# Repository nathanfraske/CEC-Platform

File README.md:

# CEC Platform

**CEC is a modular PC power-telemetry system.** Per-rail sensing modules connect
to a central Hub over a single commodity cable (RJ-45). The Hub aggregates
telemetry and forwards it to the host PC over USB. Four tiers — **Standard,
Pro, Enterprise, Mission Critical** — are built from one fundamental design with
progressively populated features.

Modules are **tier-agnostic and degrade gracefully**: any module works in any
Hub, with higher-tier features going dormant when the Hub cannot service them
and activating, without replacement, when the module is moved to a capable Hub.

This repository holds the **KiCad 10 hardware design sources** (schematics,
layouts, the shared component library), the fabrication snapshots, and the
tooling that checks them.

## PCB engineering entry points

Layout work now starts with the [frontier-directed workbench](docs/agent-directed-pcb-pipeline.md),
implemented in `src/cec_pipeline/` and exposed through one direct/MCP API.
The model authors connected placement, route and power-copper transactions;
independent native validators gate them. Legacy search engines are optional
backends, not the default decision loop.

The nine [pinned review controls](checkpoints/README.md) include portable PCB,
rule, actual footprint-library and native-report evidence. Review closure is
not manufacturing release. See the [repository module map](docs/repository-map.md)
for source, domain data, historical experiments, runtime and validation paths.

> **Ground truth.** [`CEC-Platform-Ground-Truth-Spec.md`](CEC-Platform-Ground-Truth-Spec.md)
> is the canonical specification and holds precedence over everything else,
> including [`CLAUDE.md`](CLAUDE.md). Read the spec before making any design
> decision. Spec revision: **v1.1.0 (2026-06-09), controlled baseline** (semantic
> versioning; the pre-release v1.0–v3.11 working log is retained in spec §11.1).
> Working-summary revision: **2026-06-09**.

---

## Boards

| Board | Directory | Tier | MCU | Ports | Host link | BOM target (100q) |
|---|---|---|---|---|---|---|
| Hub Standard | [`beta/hub-standard-rev2`](beta/hub-standard-rev2) | 1 | ESP32-S3-WROOM-1-N16R8 | 4 | USB Full Speed | ~$36 |
| Hub Pro | [`hubs/hub-pro`](hubs/hub-pro) | 2 | ESP32-P4 | 8 | USB High Speed | ~$45 |
| Hub Enterprise | [`hubs/hub-enterprise`](hubs/hub-enterprise) | 3 | ESP32-P4 + secure element | n/a | USB HS (+ optional 1000BASE-T1) | ~$50 |
| Hub Mission Critical | [`hubs/hub-mission-critical`](hubs/hub-mission-critical) | 4 | ESP32-P4 + crypto | n/a | redundant uplinks | ~$80 |
| 24-pin ATX module | [`beta/atx-24pin-rev3`](beta/atx-24pin-rev3) | Standard | per module spec | – | – | $35 |
| EPS 8-pin module | [`beta/eps-8pin-rev3`](beta/eps-8pin-rev3) | Standard | per module spec | – | – | $32 |
| PCIe 8-pin 2-port | [`beta/pcie-8pin-2port`](beta/pcie-8pin-2port) | Standard | per module spec | – | – | $38 |
| PCIe 8-pin 3-port | [`beta/pcie-8pin-3port`](beta/pcie-8pin-3port) | Standard | per module spec | – | – | ~$42 |
| 12VHPWR Standard module | [`beta/12vhpwr-standard`](beta/12vhpwr-standard) | Standard | per module spec | – | – | $49 |
| 12VHPWR Pro module (lead) | [`modules/12vhpwr-pro`](modules/12vhpwr-pro) | Pro | ESP32-P4 | – | – | $98–$99 |

Enterprise and Mission Critical are specified at platform-summary level only
until first customer requirements land (see **OQ-7**).

---

## The universal interface (LOCKED)

Every board — every Hub, every module, every tier — uses the same **shielded
RJ-45 (8P8C)** connector with a **locking boot** as the default shipped variant.
Mini-Fit Jr is retired platform-wide. The shared parts that implement this
interface (RJ-45 FTP jack, SK6812 LED chain, ESP32 module, power input — plus
the optional Enterprise/MC over-voltage protection network, OQ-8) live in [`lib/`](lib) so one change propagates
to every board.

### Pin allocation

| Pin | Cat5e pair | T568B color | CEC function | Tiers |
|---|---|---|---|---|
| 1 | Pair 1 | White-orange | VCC (+5VSB power) | All |
| 2 | Pair 1 | Orange | GND (power return) | All |
| 3 | Pair 3 | White-green | CAN1_H (control + low-rate telemetry) | All |
| 4 | Pair 2 | Blue | STREAM_P (RS-485 data, module → Hub) | Pro+ |
| 5 | Pair 2 | White-blue | STREAM_N (RS-485 data, module → Hub) | Pro+ |
| 6 | Pair 3 | Green | CAN1_L | All |
| 7 | Pair 4 | White-brown | AUX_REF (precision reference) | Pro+, pending OQ-3 |
| 8 | Pair 4 | Brown | DETECT / module-ID (analog single-wire sense) | All |

- **Power.** VCC is +5VSB on a single pin; GND returns on a single pin (no
  paralleling). Hubs take **bulk 5VSB on a dedicated 2-pin power-in connector**
  from the 24-pin module (spec §2.7) and distribute it to ports over RJ-45 VCC, so
  no single jack carries the trunk and per-port VCC stays comfortable. The RJ-45
  connector is still rated **≥ 1.5A**, and firmware **caps aggregate SK6812 LED
  current** (OQ-2). The VCC series protection resistor is sized together with the
  power budget, not independently.
- **Control — CAN.** All control and command traffic lives entirely on CAN, on
  pair 3, for every tier. Classical CAN at 500 kbps on Standard; CAN-FD on Pro
  and above. Transceiver TJA1051T/3; fixed **120 Ω split termination at the Hub**.
- **Streaming — RS-485.** High-bandwidth telemetry only, one direction
  (module → Hub), on pair 2. Present on **Pro modules and Pro+ Hubs only**;
  Standard leaves pair 2 unused and terminated at the module side.
- **DETECT.** Analog single-wire identity and presence sense: a precision
  resistor from pin 8 to GND on each module, read by the Hub through a fixed
  pull-up to VCC as an ADC divider. Open line ≈ VCC = no module. Resistor code
  table pending (OQ-6).
- **Protection.** Standard and Pro do **not** populate per-pin PoE/over-voltage
  protection — accidental PoE injection isn't a design target there. A per-pin
  TVS array plus series limiting resistors (PoE-survivable to ~57V) is an open
  question for Enterprise/Mission Critical (OQ-8).

See spec [§2](CEC-Platform-Ground-Truth-Spec.md) for the full interface detail.

---

## Repository layout

```
cec-platform/
  lib/                       # shared library: the locked universal interface
    cec.kicad_sym            #   symbols (authored in the KiCad Symbol Editor)
    cec.pretty/              #   footprints (RJ-45 FTP jack, SK6812, ESP32, power input; protection net is Enterprise/MC, OQ-8)
    3dmodels/                #   3D models referenced by footprints
  hubs/
    hub-standard/            # Tier 1 — ESP32-S3, 4 ports, classical CAN, USB FS
    hub-pro/                 # Tier 2 — ESP32-P4, 8 ports, classical CAN + RS-485, USB HS
    hub-enterprise/          # Tier 3 — platform-summary only for now (OQ-7)
    hub-mission-critical/    # Tier 4 — platform-summary only for now (OQ-7)
  modules/
    atx-24pin/               # Standard (superseded line)
    atx-24pin-rev2/          # Standard (current 24-pin line)
    eps-8pin/                # Standard
    pcie-8pin-2port/         # Standard (2 ports / 4 connectors)
    pcie-8pin-3port/         # Standard (3 ports / 6 connectors)
    12vhpwr-standard/        # Standard
    12vhpwr-pro/             # Pro (lead Pro module)
  fab/                       # tagged release snapshots of exactly what was sent to the board house
  firmware/                  # module firmware: shared ESP-IDF components, per-app trees, RTL
  corpus/general/            # cross-project rules corpus (SB-13; linted for provenance)
  tests/                     # pipeline unit tests + the golden-board regression (SB-08)
  docker/                    # the routing-container compute plane (kicad-cli/pcbnew 10 + JRE)
  scripts/                   # kicad-cli wrappers, CI helpers, and the agentic routing/synthesis plane
  CEC-Platform-Ground-Truth-Spec.md   # canonical spec (precedence over all)
  CLAUDE.md                  # operating guidance / working summary of the spec
  README.md
  LICENSE  NOTICE            # Apache-2.0
```

Each board is its own KiCad project. The universal-interface parts are sourced
from `lib/` rather than duplicated per board, and library tables use
project-relative paths (`${KIPRJMOD}`) — **never** absolute paths.

**Firmware lives in [`firmware/`](firmware/)** — consolidated from the
former `cec-24pin-idf` and `cec-eps-idf` repos (subtree-imported with
history) plus the 12VHPWR prototype's RTL + ESP32-P4 app: shared
ESP-IDF components under `firmware/esp/components/`, the prototype
(dev-board/perfboard) apps under `firmware/esp/proto/` — the flat
`firmware/esp/<name>` level is reserved for production apps matching
`modules/<name>` — and the GW5A acquisition RTL under `firmware/rtl/` with its
simulation gate. Pin maps live next to the KiCad projects that define
them; `firmware/FOLLOWUPS.md` tracks deferred work, and
`.github/workflows/firmware-ci.yml` builds all three apps + runs the
RTL sim on every firmware push (toolchain pins in `versions.env`).

---

## Toolchain

- **KiCad 10** (current stable, 10.0.x series). The `.kicad_*` file format is
  forward-only: a board saved in 10 will not open in 9. Keep every local install
  and any CI/container on the same major version.
- **`kicad-cli`** ships with KiCad and runs headless; it must be on `PATH`. For
  CI or a container, use the official KiCad Docker image rather than a full GUI
  install.

### Checks and outputs

Wrapper scripts in [`scripts/`](scripts) drive `kicad-cli`. Each prefers a local
`kicad-cli` and otherwise falls back to the official KiCad Docker image
(override the tag with `KICAD_IMAGE`, default `kicad/kicad:10.0`).

```bash
# Electrical rule check (schematic). Exit 0 = clean, 5 = violations.
scripts/erc.sh beta/hub-standard-rev2/hub-standard-rev2.kicad_sch

# Design rule check (layout). Exit 0 = clean, 5 = violations.
scripts/drc.sh beta/hub-standard-rev2/candidate/hub-standard-rev2-candidate.kicad_pcb

# Connectivity netlist and BOM, for checking against the spec.
scripts/netlist.sh beta/hub-standard-rev2/hub-standard-rev2.kicad_sch
scripts/bom.sh     beta/hub-standard-rev2/hub-standard-rev2.kicad_sch

# Top-side render for a quick silk/placement look.
scripts/render.sh  beta/hub-standard-rev2/candidate/hub-standard-rev2-candidate.kicad_pcb

# Fab package (gerbers + drill + pick-and-place) into the gitignored build/ dir.
scripts/fab.sh     beta/hub-standard-rev2/candidate/hub-standard-rev2-candidate.kicad_pcb

# CI sweep: ERC over every schematic, DRC over every layout. A board with a
# fab/<board>-* snapshot is ALWAYS checked, DRAFT marker or not; the gate fails
# on ERROR-level violations (warnings stay visible in the build/ reports).
scripts/check-all.sh

# Repo hygiene: no Mini-Fit Jr footprints, no absolute library paths, and the
# corpus provenance lint (corpus/general/ + scripts/constraints/).
scripts/checklist.sh
```

Reports and fab outputs are written under `build/` (gitignored). Fab packages
are committed only as tagged release snapshots under `fab/<rev>/`.

### Model-directed PCB work (Python / MCP)

Use [`src/cec_pipeline`](src/cec_pipeline) through
`python3 scripts/cec_agentic_workbench.py --workspace .cec/campaign`.
The frontier model chooses explicit geometry; independent native/current/
Kelvin/assembly receivers gate each private candidate. See the
[workflow guide](docs/agent-directed-pcb-pipeline.md) and
[repository map](docs/repository-map.md).

The old self-hosted Route/Synthesize workflows, overnight launchers, local
wave manager, legacy compute MCP registration and wave wakeup bridge are
retired. Shared CAD/physical libraries remain importable for receiving and
regression coverage, but their old autonomous CLI entry points fail closed.
Board-local `pipeline-policy.json` files own the approved requirements;
loading one no longer imports the old wave runner. Retirement inventory and
recovery instructions are in `docs/legacy-job-retirement-2026-11-05.json`.

### Self-contained & reproducible (clone parity)

A plain `git clone` is a full-parity project — no dependency on a machine's
global KiCad libraries:

- **Pinned toolchain.** The KiCad version is pinned in
  [`versions.env`](versions.env) (major 10, the 10.0.x series); the scripts and
  CI read it. The `.kicad_*` format is forward-only.
- **Vendored parts.** Official and third-party symbols/footprints are copied into
  [`lib/vendor/`](lib/vendor) and their 3D models into
  [`lib/3dmodels/`](lib/3dmodels), all referenced by `${KIPRJMOD}`-relative
  paths. `scripts/vendor-libs.sh` brings them in at the pinned library tag.
- **Enforced.** `scripts/checklist.sh` (run in CI) fails if any design file uses
  a machine-global `${KICAD*_DIR}` or an absolute path — the signal that a part
  still needs vendoring.

---

## Design-review checklist

A recurring pass, enforced in part by `scripts/checklist.sh`:

- No Mini-Fit Jr footprints remain anywhere; all module-to-Hub connectors are
  RJ-45 8P8C.
- Pinout on every board matches the locked pin allocation table above.
- PoE/over-voltage protection is not populated on Standard/Pro; on Enterprise/MC
  it follows OQ-8.
- The RS-485 pair (pins 4 and 5) and its receivers exist only on Pro and above;
  Standard leaves pair 2 unused and terminated at the module side.
- CAN termination is a fixed 120 Ω split at the Hub.
- Power-netclass trace width covers the trunk worst case; the firmware LED
  current cap is reflected in the design intent.
- Libraries and 3D models are vendored in-repo and referenced by
  `${KIPRJMOD}`-relative paths only (no machine-global or absolute paths).
- BOM totals are in line with the spec targets.

---

## Open questions

Design decisions that are **not** settled in the spec. Do not assume an answer;
surface it. Summarized here, full text in spec [§9](CEC-Platform-Ground-Truth-Spec.md).

| ID | Topic | Spec recommendation |
|---|---|---|
| OQ-1 ✓ locked | Hub bulk power → dedicated 2-pin +5VSB power-in from the 24-pin module; RJ-45 VCC distributes per-port (spec §2.7) | Resolved 2026-05-30 |
| OQ-2 | LED current cap value and max LED state to budget | Confirm a firmware cap |
| OQ-3 | Precision reference: distributed AUX_REF (pin 7) vs. local REF3033 | Path B (local REF3033) |
| OQ-4 | Cable-length SKUs and any-length policy | Pending; interacts with OQ-3 |
| OQ-5 | RS-485 topology: per-port point-to-point vs. shared multidrop | Per-port (working basis) |
| OQ-6 | Module-ID resistor encoding table | Pending module/tier list |
| OQ-7 | Fully specify Enterprise/Mission Critical now, or summary-level | Summary-level for now |
| OQ-8 | Per-pin PoE/over-voltage protection on Enterprise/MC (TVS + series-R, ~57V); Standard/Pro don't populate it | Pending Ent/MC requirements |

Two consequences worth calling out for layout work:

- With **OQ-1 locked** (dedicated 2-pin power-in), the full 5VSB trunk runs on the
  dedicated power-in and the Hub's internal distribution, while each RJ-45 VCC pin
  carries only one module. The **power-netclass minimum trace width** and the
  board `.kicad_dru` still wait on **OQ-2** (the LED cap) to fix the worst-case
  current.
- **AUX_REF on pin 7** is provisional pending **OQ-3**; treat it as such.

---

## Status

This is an early-stage hardware repository. The directory structure, shared-
library home, tooling, CI, and documentation are in place. The KiCad design
artifacts land per board over time: symbols, library-driven schematics, and
library tables can be drafted in-repo (then verified with ERC and the exported
netlist), while **PCB routing geometry** is done interactively in the KiCad 10
GUI.

**Carried action item:** the Hub Standard and 12VHPWR schematics still show
Mini-Fit Jr footprints and must be re-cut to RJ-45 before any board order. They
are the stale artifacts; the spec is current.

---

## Contributing

- The spec wins. If a change to a locked decision seems warranted, propose a
  spec revision first rather than diverging in a board.
- Do not resolve an open question (OQ-1…OQ-7) by assumption — surface it.
- Keep library paths project-relative (`${KIPRJMOD}`); never commit absolute
  paths. Vendor any official/third-party part you use
  (`scripts/vendor-libs.sh`) so a clone stays self-contained, and keep the
  toolchain on the pinned KiCad 10 (`versions.env`).
- Run `scripts/check-all.sh` and `scripts/checklist.sh` before pushing layout or
  schematic changes.
- Commit fab outputs only as tagged release snapshots under `fab/<rev>/`, not as
  routine churn.

---

## License

Copyright 2026 Nathan M. Fraske.

Licensed under the **Apache License, Version 2.0**. You may not use the files in
this repository except in compliance with the License. See [`LICENSE`](LICENSE)
for the full text and [`NOTICE`](NOTICE) for attribution; a copy of the License
is also available at <http://www.apache.org/licenses/LICENSE-2.0>.

Unless required by applicable law or agreed to in writing, work distributed
under the License is distributed on an "AS IS" BASIS, WITHOUT WARRANTIES OR
CONDITIONS OF ANY KIND, either express or implied.

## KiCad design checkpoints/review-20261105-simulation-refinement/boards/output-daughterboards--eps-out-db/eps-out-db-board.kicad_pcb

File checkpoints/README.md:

# Native review controls

`current.json` pins one receipt by its exact SHA-256, never by file age. The
November 4 snapshot contains nine saved PCB families, their actual footprint
libraries, fresh native DRC reports, original reports and source provenance.
It is a portable review checkpoint, **not a fabrication release**. Its native
totals are zero opens, zero errors, zero exclusions and 283 warnings. Retained
EPS field-policy findings are separate from native DRC.

`review-20261104-final` preserves the pre-overhaul layout controls.
`review-20261104-overhaul` adds the independently received, visually reviewed
Hub route-shortening pilot; all other board geometry is identical. Its origin
receipt retains the explicit work order, parent/child identities and plot
identities. `current.json` selects this newer review checkpoint explicitly.

The frontier-directed workbench copies these controls into private jobs. It
cannot overwrite them or silently select a different schematic/PCB revision.
`fork` changes only the campaign's selected working parent after receiving
and visual review. Runtime jobs and plots belong outside this directory.

Footprint-library URIs are relocated; actual footprint file bytes, library
names and enable flags are retained. No library is synthesized from the
embedded board pads. A fresh checkout requires KiCad 10.x and the documented
native reporting build to repeat measurements, but not the original author's
Windows review directory to inspect the saved evidence.

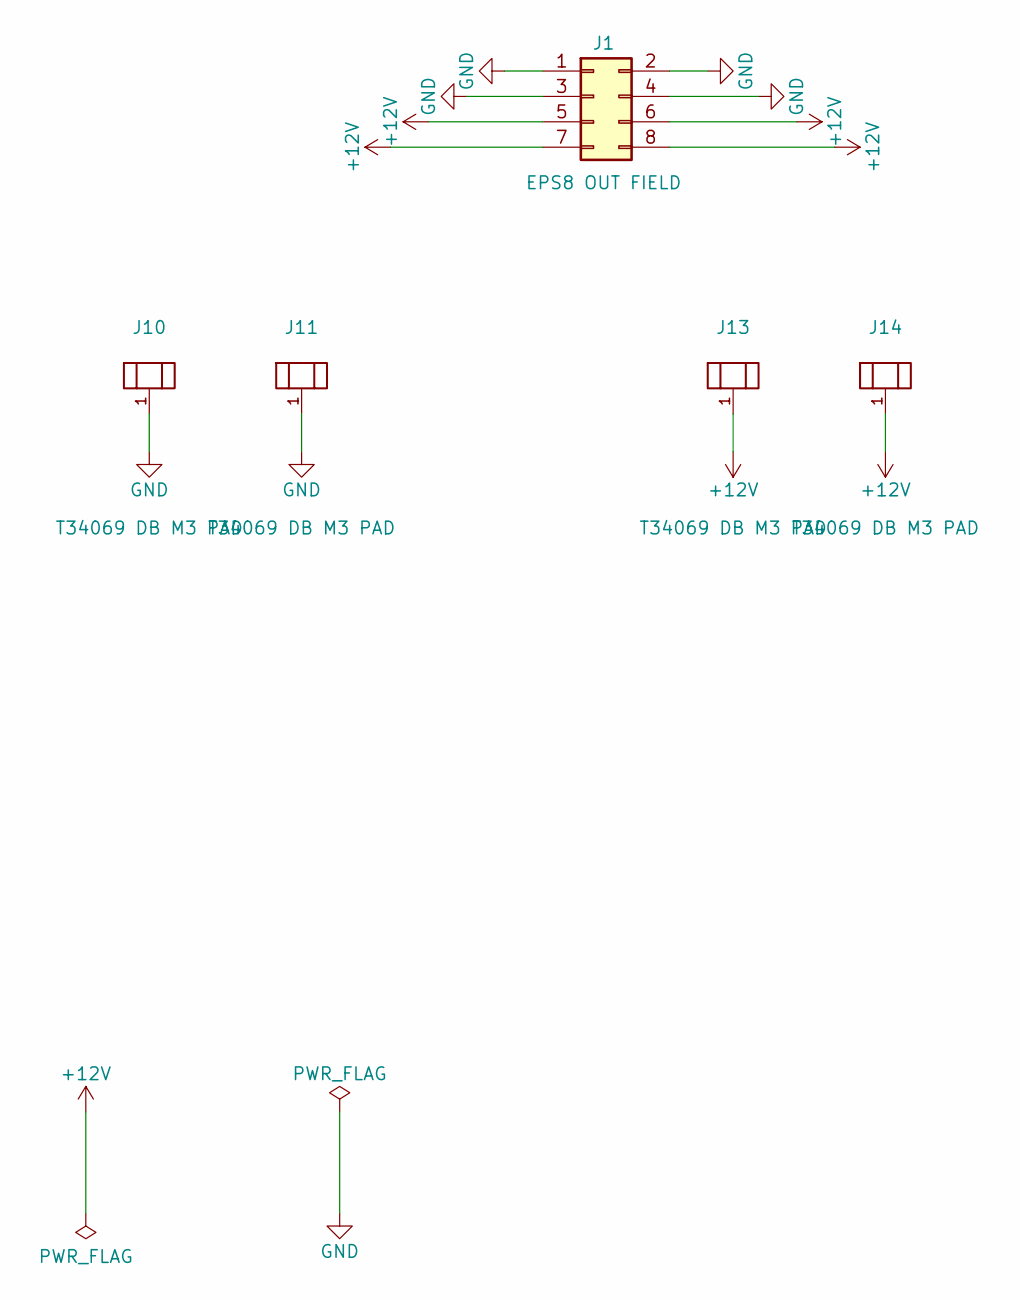
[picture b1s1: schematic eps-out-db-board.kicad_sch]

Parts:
J1: EPS8 OUT FIELD; EPS8_Daughterboard_Field_P4.20mm
J10, J11, J13, J14: T34069 DB M3 PAD; XFCN_T34069_Daughterboard_BoltPad_M3_PROVISIONAL

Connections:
+12V: J1.5, J1.6, J1.7, J1.8, J13.1, J14.1
GND: J1.1, J1.2, J1.3, J1.4, J10.1, J11.1

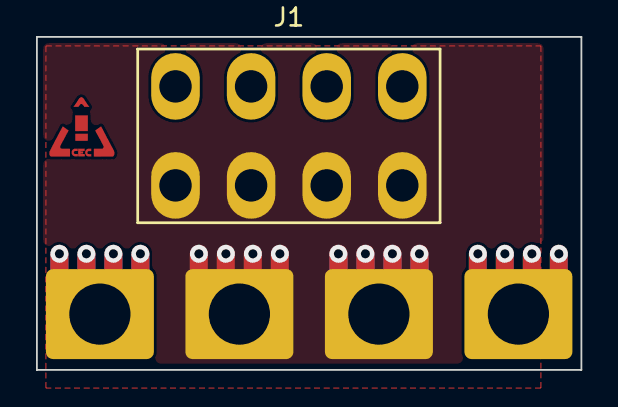
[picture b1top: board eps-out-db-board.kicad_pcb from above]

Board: 4 copper layers, 30.2 x 18.5 mm, 6 parts (0 on the bottom side), 2 nets.

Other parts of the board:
LOGO1: CEC_Logo_Copper_Small

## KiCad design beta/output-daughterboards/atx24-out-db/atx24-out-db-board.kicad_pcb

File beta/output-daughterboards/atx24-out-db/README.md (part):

# 24-pin ATX output daughterboard — BETA-1

> **XFCN PROTOTYPE SUPERSESSION (2026-08-12):** the live schematic and PCB now
> use four XFCN T34069 M3 bolt pads for `+12V`, `+5V`, `+3V3`, and `+5VSB`,
> plus two XFCN TTR32100127-0600 M3 bolt pads for `GND`. The TE blade history
> below remains as design provenance, not current implementation authority.
> The former PCB-only `SR1`–`SR6` pads were no-net placeholders, did not form a
> measurement circuit, and are retired. A future connector-health/remote-sense
> feature must be introduced as a complete schematic, mating, ADC-protection,
> and firmware contract rather than as anonymous copper provisions. See
> `docs/standard-xfcn-terminal-integration-handoff-2026-08-12.md`.
> The live compact outline is **54.0 × 21.3 mm** (11.8% less area than the
> 61.0 × 21.38 mm predecessor). The four control circuits now use a compact
> **Samtec TSW-102-16-G-D-RA 2×2 right-angle male**, mating the main board's
> **SSQ-102-03-G-D 2×2 vertical socket**. Pin order is Samtec odd/even by
> column: 1=`-12V`, 2=`PS_ON#`, 3=`PWR_OK`, 4=`GND`. The `-16` style's
> 8.13 mm mating length satisfies the calculated ≥6.4 mm engagement floor;
> first-article alignment and engagement remain required.

Passive connector-daughterboard for the 24-pin ATX module's OUTPUT side, per
spec **§2.8 v1.4.0** (`CEC-Platform-Ground-Truth-Spec.md`) and the owner
ruling `docs/standard-tier-review/SYNTHESIS-beta-plan.md` §D-5a. Mates with
the main board's `TB1`–`TB9` Keystone 3586 universal blade clips (TB symbols
exist in `modules/atx-24pin-rev3`'s **schematic**, commit `b76a62a`; **no
clip placement exists on any main-board PCB yet** — this board's tab grid is
the authoritative mating drawing, see "Keying") and reproduces the full
24-circuit ATX output pin map for a bare pigtail or a future MODDIY-class
vertical header. **No active or passive components** — connector bodies and
fan-out copper only, per the ratified "no components beyond the connector
body and its fan-out copper" text.

> **ITERATION 7 (2026-07-06, owner-ratified) — READ FIRST, supersedes the
> iteration-5 numbers below where they differ.** Main-board mate changed:
> Keystone **3557 clip → TE 63969-1 FASTON .250 PCB RECEPTACLE** (vertical/
> top entry; the DESIGNED mate for the 63951-1 blade — rev-E dwg note 3
> puts our 0.81 mm thickness at its design centre, retiring the
> 27%-over-centre fit item; 22.9 A @ 30 °C rise per TE 108-1706; 63968-1 =
> same-land low-insertion-force fallback; LCSC C2961150, stock ~5 =
> restock watch, DigiKey depth). **ORIENTATION (owner requirement, proven
> from `lib/datasheets/TE_63969_customer_drawing_revE.pdf` and
> checker-asserted):** the receptacle's two Ø1.40 holes at 5.08 mm pitch
> run **perpendicular to the row**, along the descending blade's plane —
> plan-congruent with the blade's own leg holes; the blade's bottom edge
> enters the slot edge-wise. Along-row footprint is therefore only the
> receptacle's ~3.7 mm across-thickness depth (UN-DIMENSIONED on rev E —
> **depth ≤ 4.0 mm is the #1 sample-gate item; above it, atx24 falls back
> to a 6.3 pitch**): pitch floor 3.7 + 0.5 = **4.2 mm**; pitches now
> **atx24 4.2 / eps 4.7 / pcie 5.2**. Joint counts re-ratified at
> 22.9 A/125% (18.32 A allowable per joint): **atx24 10 tabs** (3V3 gains a
> second joint at 24.0 A basis; GND ×4 = 18.0 A/joint = 127% hairline,
> surfaced), **eps holds 6/cable** (17.33 A = 132%), **pcie 6/cable**
> (3/polarity; 2/polarity was 19.5 A = 117% FAIL). Boards: **atx24 61.0 ×
> 21.4, eps 28.5 × 20.0, pcie 31.0 × 20.0 mm** (pcie GROWS — the +2
> ratified joints outweigh its pitch win; honest number). Seating: float
> 12.41 mm unchanged; the 8.38 mm receptacle top is cleared by **4.03 mm**;
> detent-hole engagement at nominal float is NOT established (retention may
> be spring-friction only — sample item, with gang insertion force). Full
> record: `docs/standard-tier-review/blade-fit-check-2026-07-04.md`
> **addenda 6–7**.

> **ITERATION 5 (2026-07-05, owner) — READ FIRST, supersedes the iteration-4
> numbers below where they differ.** Main-board clip part changed: Keystone
> **3586 (SMD) → 3557 bare top-entry clip** (THT, UL 30 A @ 500 V AC; the
> "3557-2" this repo vendored earlier is the 2-in-1 HOUSED holder, a
> different product — naming corrected; 3586 stays vendored as the SMD
> fallback). Clip rotated slot-perpendicular-to-wall; its **leg pair runs
> ALONG the row** (verified from the catalog mounting details — this
> contradicts the leg-parallel-to-jaw assumption and caps the win): pitch
> floor = 3.4 leg pitch + 2.4 pad + 0.5 solder web = **6.3 mm**, pitches now
> **atx24 6.3 / eps 6.7 / pcie 7.2** (keying margins 1.00/0.75/1.35, teeth
> re-verified). Boards: **atx24 69.5 × 21.4, eps 38.5 × 20.0, pcie 26.6 ×
> 20.0 mm**. Seating: uniform 4.34 mm leg row, float 12.41 mm at 1.0 mm tip
> clearance; the taller 10.2 mm clip's top is cleared by 2.21 mm; engagement
> now spans the clip's full interior. atx24 also swaps its signal stub: the
> 2×5 header is RETIRED for a **1×4 right-angle blind-mate pin header**
> (long-tail Dupont class, pins down past the edge parallel to the blades,
> single-motion drop-in; NEW pin map 1=−12V, 2=PS_ON#, 3=PWR_OK, 4=GND) plus
> **six DNP sense-return pads SR1–SR6** (OQ-88 provision form only). #1
> fit-check item: the 0.81 mm FASTON tab is ~27% over the clip's 0.64 mm
> fuse-blade design centre (inside the published .020–.032 acceptance, at
> its ceiling — stiffer grip expected, sample-gated). Full record:
> `docs/standard-tier-review/blade-fit-check-2026-07-04.md` **addendum 5**.

DRAFT (no fab yet — the OQ-86 physical fit-check sample gate is still open).

## Posture — vertical card, tabs blade-DOWN (owner sketch, 2026-07-05)

This board is a small vertical card standing perpendicular to the main board
(owner ruling 2026-07-04/05, unchanged). The connector form went through
three same-day iterations on 2026-07-05 and is settled by the **owner's
sketch** (the final ruling; the two earlier forms — TE 63849-1
straight-tab/side-entry, then a mis-modeled "blade hangs past the edge
in-plane" reading of the 63951-1 — are retired, record in
`docs/standard-tier-review/blade-fit-check-2026-07-04.md` addendum 3):

The tabs are **TE 63951-1** (RIGHT-ANGLE FASTON .250 — "the blade that has
the 90 degree rotation in it," owner). The part is a flat in-plane **L
stamping**: the blade runs along the leg-pitch axis past the blade-side leg,
standing **2.54–8.89 mm off its seating face** (TE dwg C=63951 rev L2,
`lib/datasheets/TE_63951-1.pdf`). Mounted per the sketch: the two legs go
**horizontally** through this board's face, the 5.08 mm leg pitch runs
**vertically** (legs stacked one above the other), and the blade therefore
points **straight down**, descending past this board's bottom edge at the
2.54–8.89 mm Z-standoff — *"It needs to align vertically so it can actually
point down and slot into the clip."* The whole assembly drops vertically;
each blade enters its main-board Keystone 3586 clip's **top-entry** jaws
broadside (the clip's native auto-blade-fuse mode, Keystone dwg 3586). The
board's own bottom edge **floats clear of the main board** — *"the TAB does
the reaching down, not the board"* — no board material or copper crosses
Edge.Cuts; only the tab's off-board descender passes below the edge level,
offset from the board plane with no conflict.

**Board axes**: X = length (FREE dimension, minimized opportunistically);
Y = height. **The ≤15 mm height cap is EXPLICITLY RELAXED by the owner for
the iteration-4 compact form** (owner follow-up on the 145 mm iteration-3
board: *"Good lord those are long, can the agent stack the blades right
next to each other and put them below the pinout? That should tell us how
tall these are really going to be"*) — the deliverable is the honest
minimum height of the two-band stack.

**Measured final size**: **69.5 × 21.4 mm** (length × height). The tab row
returned BELOW the field (two-band stack: field + corridor on top, packed
tab row underneath), halving the length (145.1 → 72.8 mm) at a true height
cost of 13.6 → 21.4 mm. Height decomposition (all measured constants):
0.4 top margin + 10.2 field + 0.1 gap + 2.25 corridor (4 In2 lanes) +
0.3 lane-to-pad clearance + 7.58 tab pad band (2 × 3.79) + 0.55 edge
margin. Length is now tab-row-driven (9 × 8.4 mm + margins ≈ 73, just over
the field+header band's ~68).

## Mating geometry / seating model (iteration-4 numbers)

All numbers from `scripts/gen-output-daughterboard.py seating_report()` and
the two vendored drawings; the seating invariant is now the leg-row height
ABOVE THE BOTTOM EDGE, **uniform across all three families** (the tab band
is the lowest thing on every board; asserted by the check script):

- **Leg row** (leg-pair midpoint): **4.34 mm above the bottom edge**
  (= 3.79 pad extent + 0.55 edge margin; the lower pad's copper clears the
  board's 0.5 mm copper-to-edge constraint by 0.05 mm — sized off the
  iteration-3 `copper_edge_clearance` lesson, asserted by the checker).
- **Blade standoff** (unchanged): descender hangs 2.54–8.89 mm off the
  front face; main-board **clip slot centreline at 5.72 mm** from the wall
  plane, slot axis PERPENDICULAR to the wall line; blade width 6.35 mm vs.
  the clip's rated ≤6.4 mm accepted-tab range; slot opening 1.57 mm vs.
  0.77–0.83 mm blade thickness — ~2× clearance.
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
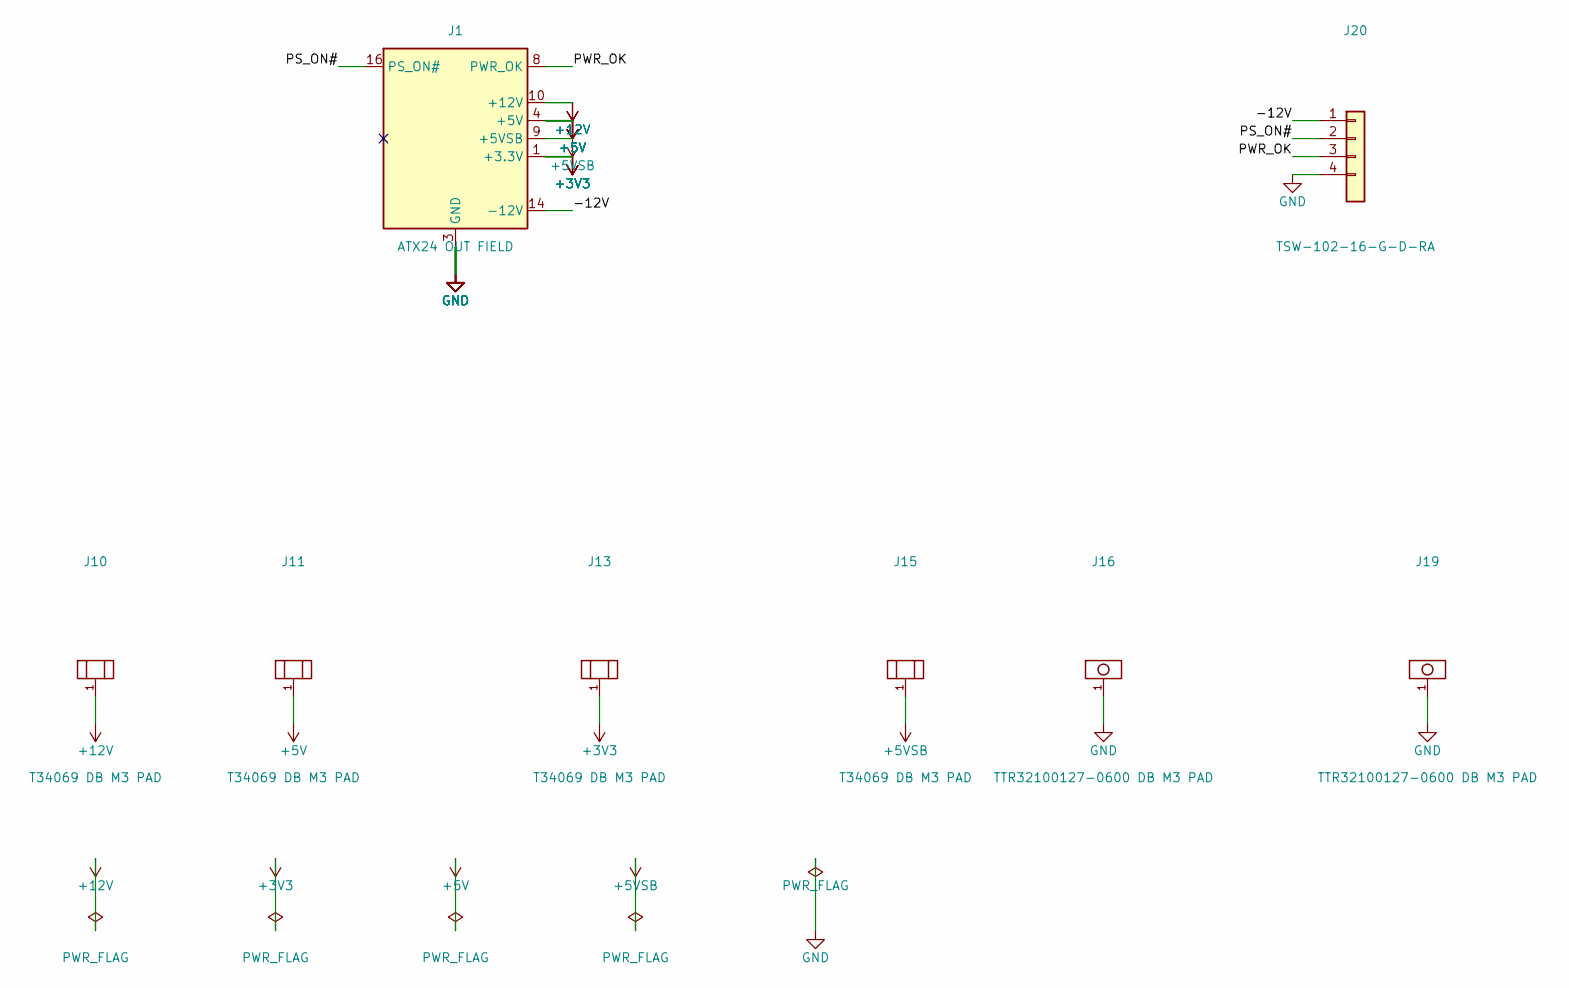
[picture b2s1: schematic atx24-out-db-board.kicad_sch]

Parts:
J1: ATX24 OUT FIELD; ATX24_Daughterboard_Field_P4.20mm
J10, J11, J13, J15: T34069 DB M3 PAD; XFCN_T34069_Daughterboard_BoltPad_M3_PROVISIONAL
J16, J19: TTR32100127-0600 DB M3 PAD; XFCN_TTR32100127-0600_Daughterboard_BoltPad_M3_PROVISIONAL
J20: TSW-102-16-G-D-RA; Samtec_TSW-102-16-G-D-RA_2x02_P2.54mm_Horizontal; MPN TSW-102-16-G-D-RA

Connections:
+3V3: J1.1 (+3.3V), J1.2 (+3.3V), J1.12 (+3.3V), J1.13 (+3.3V), J13.1
+5V: J1.4 (+5V), J1.6 (+5V), J1.21 (+5V), J1.22 (+5V), J1.23 (+5V), J11.1
+5VSB: J1.9 (+5VSB), J15.1
+12V: J1.10 (+12V), J1.11 (+12V), J10.1
/-12V: J1.14 (-12V), J20.1
/PS_ON#: J1.16 (PS_ON#), J20.2
/PWR_OK: J1.8 (PWR_OK), J20.3
GND: J1.3 (GND), J1.5 (GND), J1.7 (GND), J1.15 (GND), J1.17 (GND), J1.18 (GND), J1.19 (GND), J1.24 (GND), J16.1, J19.1, J20.4

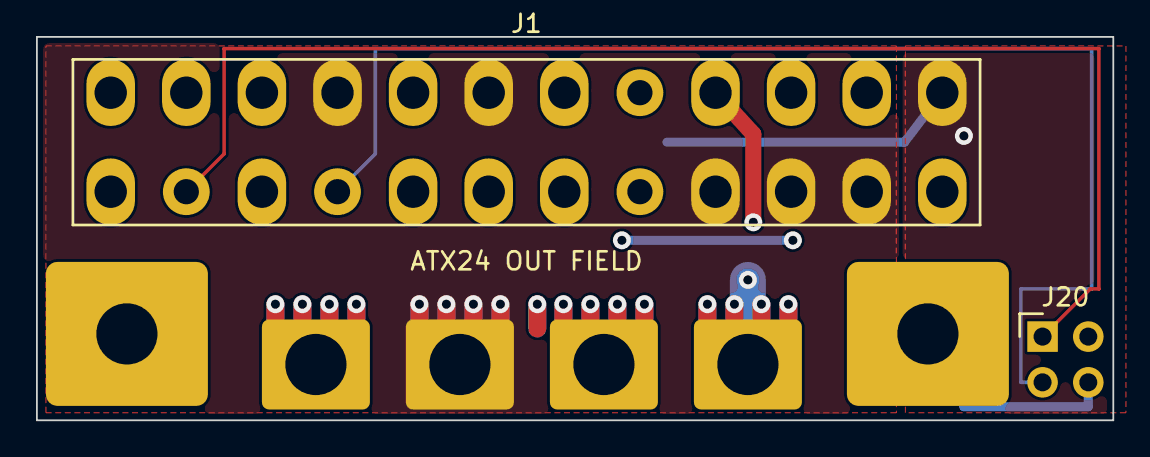
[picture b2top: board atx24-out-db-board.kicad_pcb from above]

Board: 4 copper layers, 59.8 x 21.3 mm, 8 parts (0 on the bottom side), 8 nets.

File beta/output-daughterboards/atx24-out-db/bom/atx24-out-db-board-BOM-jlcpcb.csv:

"Comment","Designator","Footprint","LCSC Part #"
"ATX24 OUT FIELD","J1","cec-Connector_Generic:ATX24_Daughterboard_Field_P4.20mm",""
"TSW-102-16-G-D-RA","J20","cec-Connector_PinHeader_2.54mm:Samtec_TSW-102-16-G-D-RA_2x02_P2.54mm_Horizontal",""

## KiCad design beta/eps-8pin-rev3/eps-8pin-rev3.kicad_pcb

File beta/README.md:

# CEC beta line — the authoritative board versions

Single source of truth for the CURRENT Standard-line beta products.  The
machine-readable equivalent is `scripts/cec_beta_manifest.py`; audits and waves
consume that manifest instead of recursively discovering whatever happens to be
under `beta/`.

**Rule:** for any beta-line change, edit only a manifest-declared directory
below.  Historical captures live under `old-revisions/` and are never project
discovery inputs.  `eps-8pin-rev3` is the one EPS product; `rev3` identifies its
current design revision, not a product variant.

> **PHYSICAL MOVE EXECUTED 2026-07-22** (owner directive: "the BETA line in its own
> directory... no further confusion on where the latest ones are" — supersedes the
> earlier defer-the-move note). The live beta lineage now LIVES in `beta/<board>/`
> (depth-preserved: 2-deep like `modules/<board>/`, so every `${KIPRJMOD}/../../lib`
> path resolves unchanged; the out-daughterboards keep depth 3 under
> `beta/output-daughterboards/`). The rule is now brutally simple: **if it's in
> `beta/`, it's the latest; everything under `modules/`/`hubs/` is alpha or
> history.** Verification of the move: normalized netlists BYTE-IDENTICAL pre/post
> for all 11 moved boards (only path metadata differs), zero stale toolchain refs
> (60-file sweep + 11 composed-path fixes + 3 resolvers: `cec_router.find_board`,
> `cec_facts.board_catalog`, `cec_synth_pipeline.Config.load` — all scan `beta/`
> first), full checklist green, SB-08 golden unchanged.

## Authoritative beta boards (edit these)

| Board | Directory | MCU | State | Markers |
|---|---|---|---|---|
| 24-pin ATX | `beta/atx-24pin-rev3` | ESP32-C6-MINI-1 | INA238 beta, DRAFT | BETA |
| EPS 8-pin | `beta/eps-8pin-rev3` | ESP32-C6-MINI-1 | current hierarchical beta, DRAFT | BETA |
| PCIe 8-pin 2-port | `beta/pcie-8pin-2port` | ESP32-C6-MINI-1 | hierarchical beta, DRAFT | BETA |
| PCIe 8-pin 3-port | `beta/pcie-8pin-3port` | ESP32-C6-MINI-1 | hierarchical beta, DRAFT | BETA |
| 12VHPWR Standard | `beta/12vhpwr-standard` | ESP32-S3-MINI-1 | hierarchical, fab-ready | BETA |
| ARGB Standard | `beta/argb-standard` | ESP32-S3-MINI-1 | beta, DRAFT | BETA |
| Hub Standard | `beta/hub-standard-rev2` | ESP32-S3-WROOM-1 | current hierarchical schematic, layout via waves | BETA |
| Smoke Tester | `beta/smoke-tester` | NONE (pure analog, by design) | sketch-stage: README spec + assets + BOM, no capture yet (owner standup 2026-07-24) | BETA + DRAFT |

The shipped Hub alpha and the earlier sectioned Hub draft are archived at
`old-revisions/hubs/hub-standard-alpha` and
`old-revisions/hubs/hub-rev2-sectioned-draft`.  They remain recoverable through
git but cannot be selected as current BETA inputs.

Output daughterboards (per the D-5a architecture, also beta and authoritative):
`beta/output-daughterboards/atx24-out-db`, `.../eps-out-db`, `.../pcie-out-db`.

## Superseded (do not edit; kept only as history)

| Stale directory | Superseded by | Why |
|---|---|---|
| `old-revisions/beta/eps-8pin-pre-rev3` | `beta/eps-8pin-rev3` | obsolete EPS revision; archived to enforce one current EPS |
| `modules/pcie-8pin-2port-rev2` | `beta/pcie-8pin-2port` | same |
| `modules/pcie-8pin-3port-rev2` | `beta/pcie-8pin-3port` | same |
| `old-revisions/hubs/hub-standard-alpha` | `beta/hub-standard-rev2` | shipped alpha reference, not a BETA editing root |
| `old-revisions/hubs/hub-rev2-sectioned-draft` | `beta/hub-standard-rev2` | older DRAFT, fewer parts, superseded |
| `old-revisions/beta/*-flat-2026-08-02` | corresponding hierarchy | reviewed electrical source retained for exact hierarchy regression |

Each carries a `SUPERSEDED` marker. None was ever fabbed. Safe to delete once you
confirm you want them gone; git history keeps them.

## Hub rev2 line (NOT superseded — the merged-in pipeline branch's hub revision)

`beta/hub-standard-rev2` (DRAFT) is the **rev2 Hub Standard schematic** finalized
2026-07-15 on `claude/pipeline-consolidation` and merged 2026-07-17: F1–F4 per-port
polyfuses, D8/D9 SMAJ5.0A power-entry TVS, C18–21 DETECT filters, the J6 column-paired
mezzanine header (DNP THT — since split into the J6P/J6C/J6D structural segments,
2026-07-22), D-11 DRU exception. Committed layout is unstarted; the wave pipeline
synthesizes its layouts (first-ever routed hubs landed 2026-07-20/22). PROMOTED into
the authoritative table 2026-07-22 (see the table note). Do NOT confuse it with
the archived `old-revisions/hubs/hub-rev2-sectioned-draft` capture.

## Alpha / ordered prototypes (keep as history, not part of the beta line)

- `modules/atx-24pin` — alpha, the validated prototype (INA228).
- `modules/atx-24pin-rev2` — the ordered rev2 prototype (INA228, physically built).

These are the alpha lineage. Per the alpha/beta convention they are never overwritten
or edited for beta work; the beta 24-pin is `atx-24pin-rev3`.

## Other tiers (not Standard beta, listed so they are not mistaken for it)

`hubs/hub-pro`, `hubs/hub-enterprise`, `modules/12vhpwr-pro`, `modules/ent-common`,
`modules/ent-kvm-carrier`.

## Move record (2026-07-22)

The deferred physical move was executed per this file's own recipe: `git mv` of the
9 authoritative dirs (+`eps-8pin-rev3`), a guarded longest-first reference sweep (60
files; `(?!-rev)` lookaheads protect the `-rev2` superseded siblings), 11
composed-path fixes (`os.path.join(ROOT, "modules", board)` forms the sweep cannot
see), and `beta/`-first search order in the three resolvers. Proofs: 11/11
normalized-netlist identity, zero stale refs in scripts/tests/.github/ops, checklist
green, golden signature unchanged. The superseded/alpha directories deliberately did
NOT move — history stays where it happened.

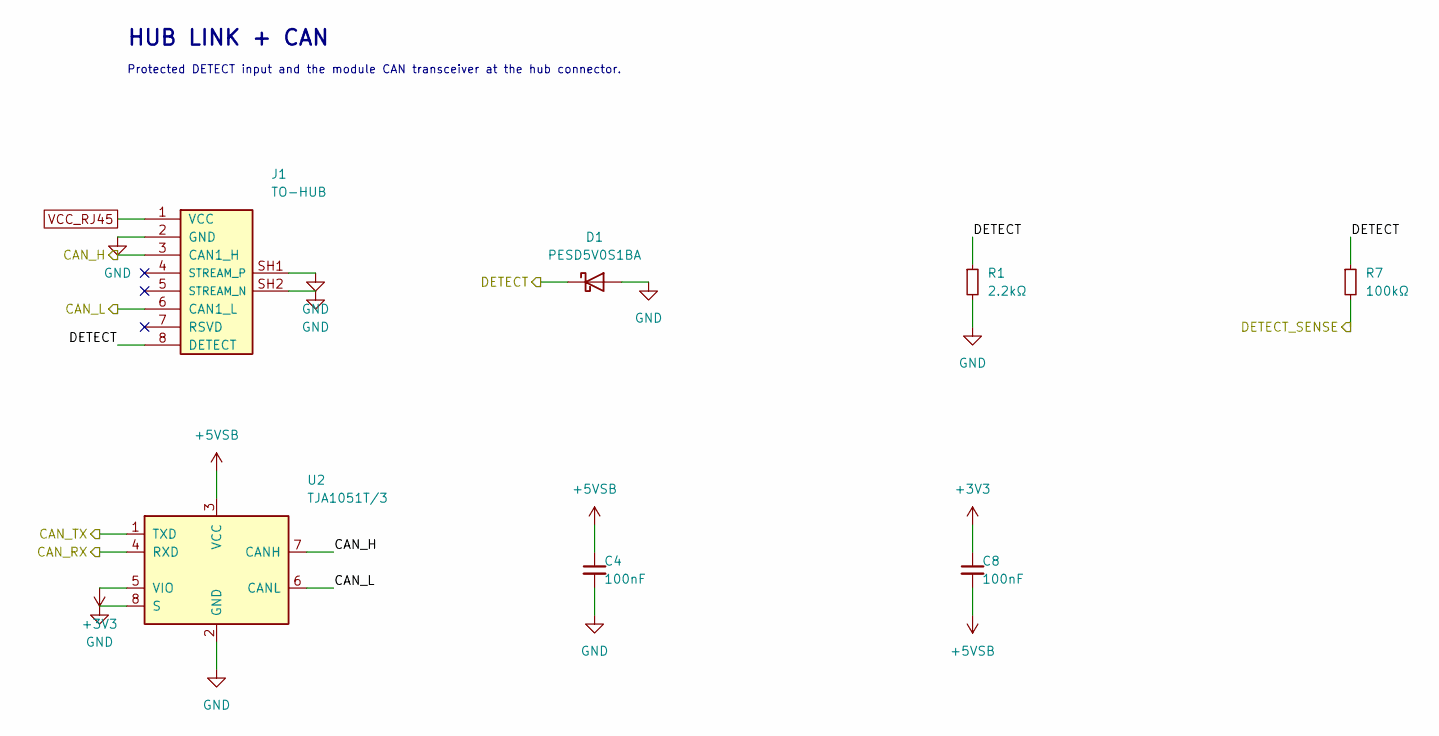
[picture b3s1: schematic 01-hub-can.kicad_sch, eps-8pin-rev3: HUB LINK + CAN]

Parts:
C4, C8: 100nF; C_0402_1005Metric; MPN CL05B104KO5NNNC; LCSC C1525
D1: PESD5V0S1BA; D_SOD-323; MPN PESD5V0S1BA; LCSC C5261083
J1: TO-HUB; RJ45_FTP_Shielded_Horizontal; MPN KH-RJ45-58-8P8C; LCSC C2683360
R1: 2.2kΩ; R_0402_1005Metric; MPN 0402WGF2201TCE; LCSC C25879
R7: 100kΩ; R_0402_1005Metric; MPN 0402WGF1003TCE; LCSC C25741
U2: TJA1051T/3; SOIC-8_3.9x4.9mm_P1.27mm; MPN TJA1051T/3/1J; LCSC C38695

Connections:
+3V3: C8.1, U2.5 (VIO); also elsewhere on the board
/CAN_H: J1.3 (CAN1_H), U2.7 (CANH)
/CAN_L: J1.6 (CAN1_L), U2.6 (CANL)
/CAN_RX: U2.4 (RXD); also elsewhere on the board
/CAN_TX: U2.1 (TXD); also elsewhere on the board
/DETECT: D1.1 (K), J1.8 (DETECT), R1.1, R7.1
/DETECT_SENSE: R7.2; also elsewhere on the board
VCC_RJ45: J1.1 (VCC); also elsewhere on the board

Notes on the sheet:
HUB LINK + CAN
Protected DETECT input and the module CAN transceiver at the hub connector.

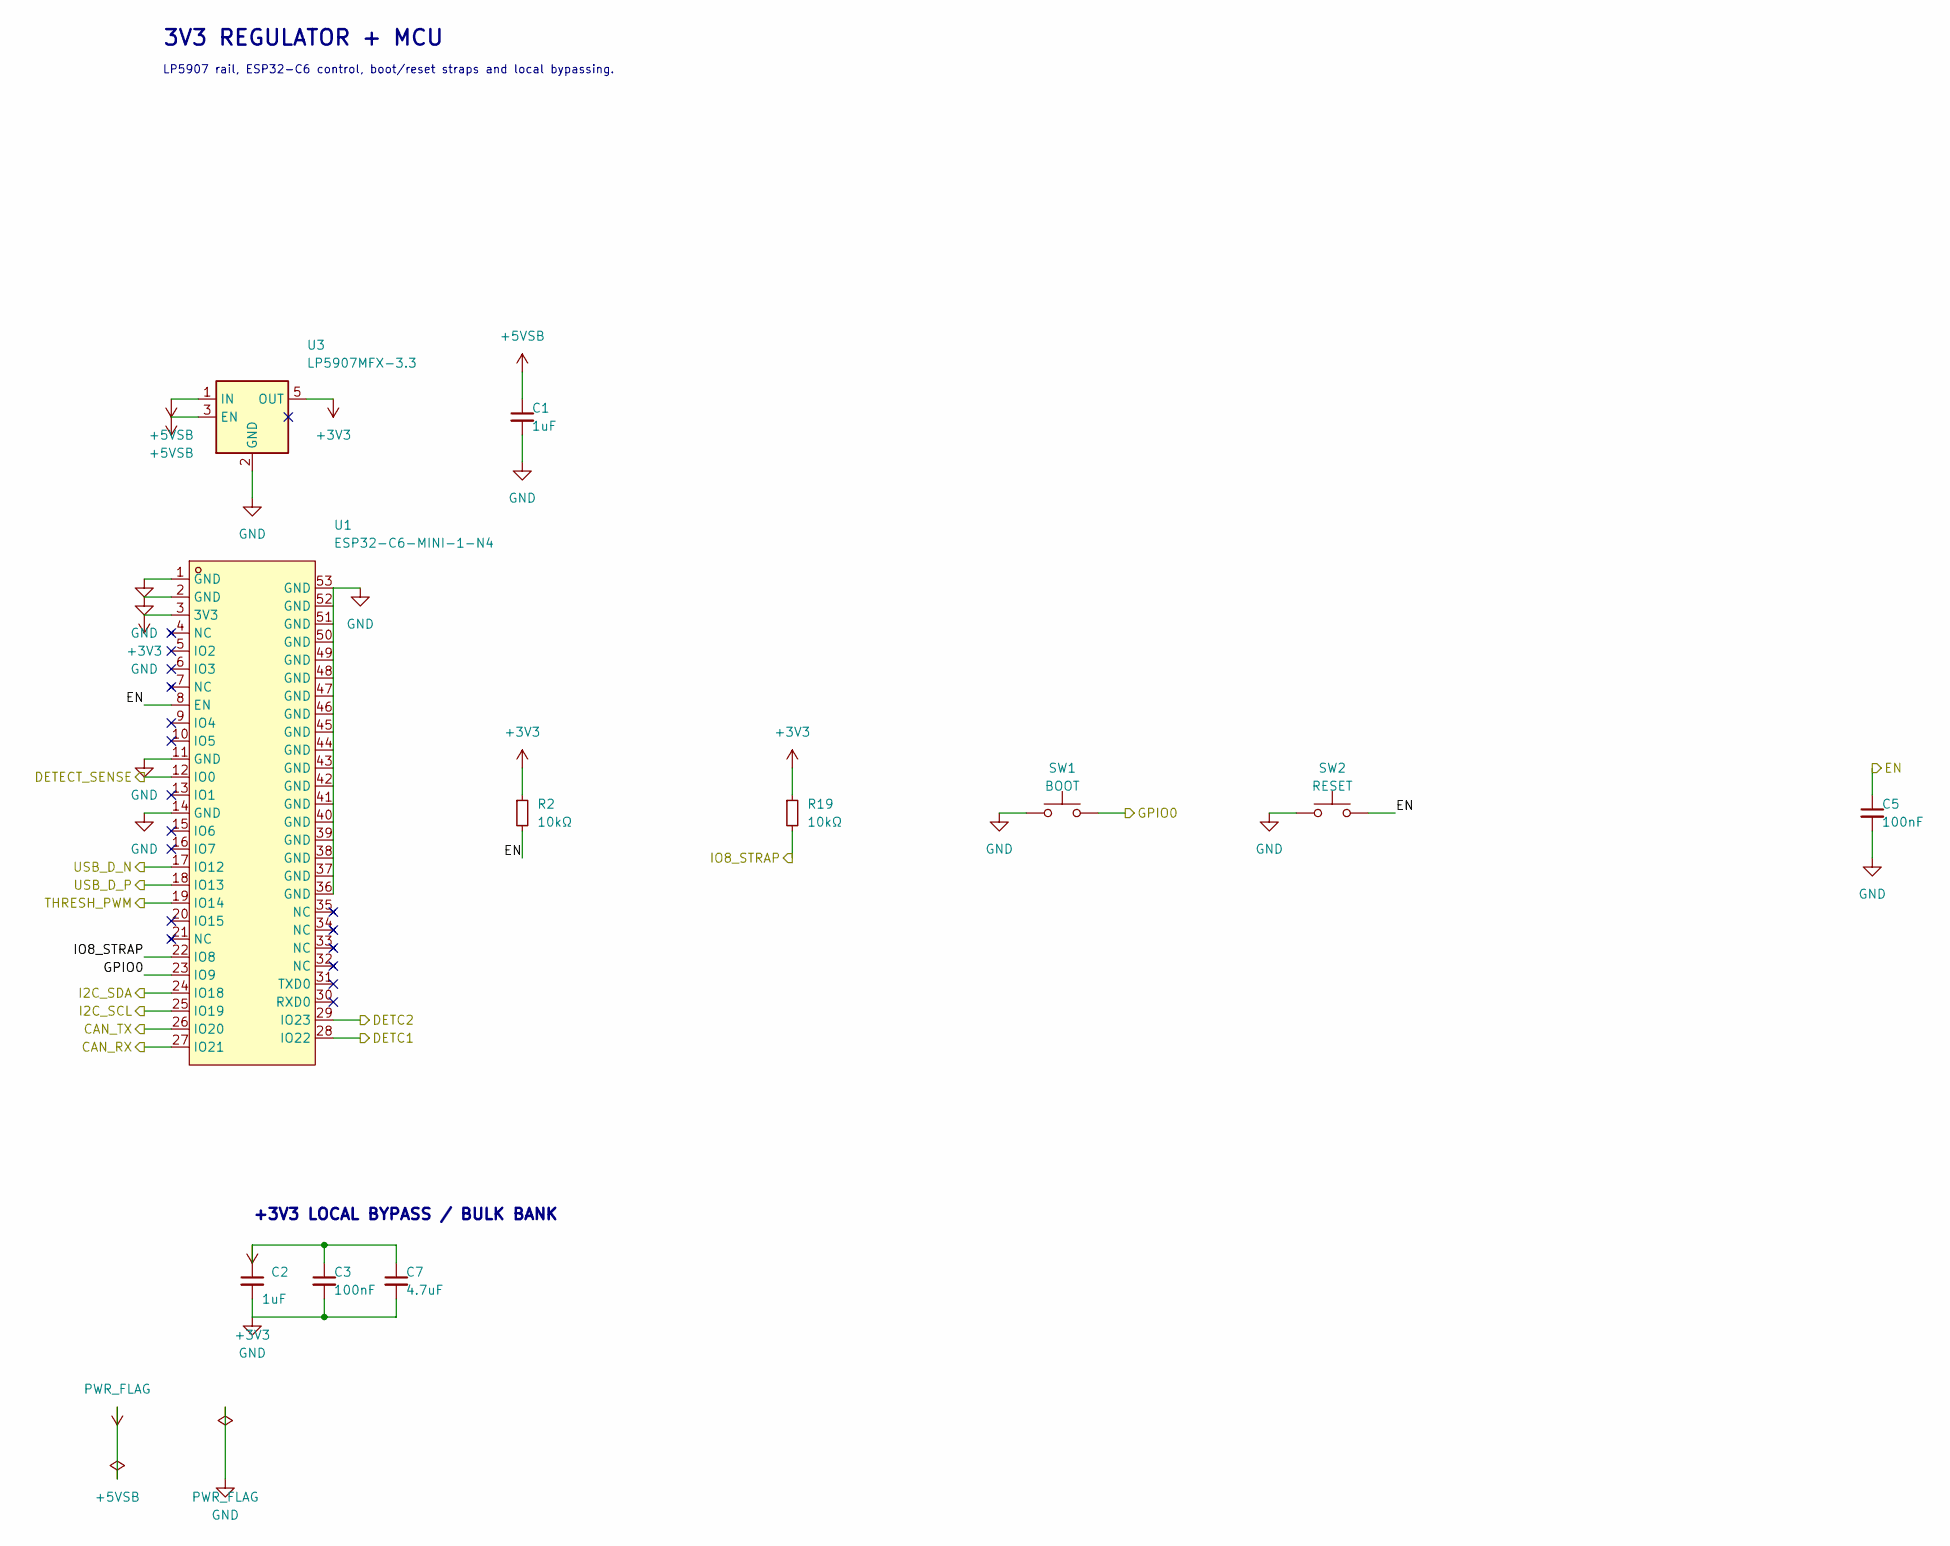
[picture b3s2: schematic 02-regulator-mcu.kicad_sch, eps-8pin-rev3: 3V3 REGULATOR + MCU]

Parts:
C1, C2: 1uF; C_0603_1608Metric; MPN CL10A105KB8NNNC; LCSC C15849
C3, C5: 100nF; C_0402_1005Metric; MPN CL05B104KO5NNNC; LCSC C1525
C7: 4.7uF; C_0805_2012Metric; MPN CL21A475KAQNNNE; LCSC C1779
R2, R19: 10kΩ; R_0402_1005Metric; MPN 0402WGF1002TCE; LCSC C25744
SW1: BOOT; TS-1088-AR02016; MPN TS-1088-AR02016; LCSC C720477
SW2: RESET; TS-1088-AR02016; MPN TS-1088-AR02016; LCSC C720477
U1: ESP32-C6-MINI-1-N4; ESP32-C6-MINI-1; MPN ESP32-C6-MINI-1-N4; LCSC C5736265
U3: LP5907MFX-3.3; SOT-23-5; MPN LP5907MFX-3.3/NOPB; LCSC C80670

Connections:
+3V3: C2.1, C3.1, C7.1, R2.1, R19.1, U1.3 (3V3), U3.5 (OUT); also elsewhere on the board
/CAN_RX: U1.27 (IO21); also elsewhere on the board
/CAN_TX: U1.26 (IO20); also elsewhere on the board
/DETC1: U1.28 (IO22); also elsewhere on the board
/DETC2: U1.29 (IO23); also elsewhere on the board
/DETECT_SENSE: U1.12 (IO0); also elsewhere on the board
/EN: C5.1, R2.2, SW2.2, U1.8 (EN)
/GPIO0: SW1.2, U1.23 (IO9)
/I2C_SCL: U1.25 (IO19); also elsewhere on the board
/I2C_SDA: U1.24 (IO18); also elsewhere on the board
/IO8_STRAP: R19.2, U1.22 (IO8)
/THRESH_PWM: U1.19 (IO14); also elsewhere on the board
/USB_D_N: U1.17 (IO12); also elsewhere on the board
/USB_D_P: U1.18 (IO13); also elsewhere on the board

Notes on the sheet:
3V3 REGULATOR + MCU
LP5907 rail, ESP32-C6 control, boot/reset straps and local bypassing.
+3V3 LOCAL BYPASS / BULK BANK

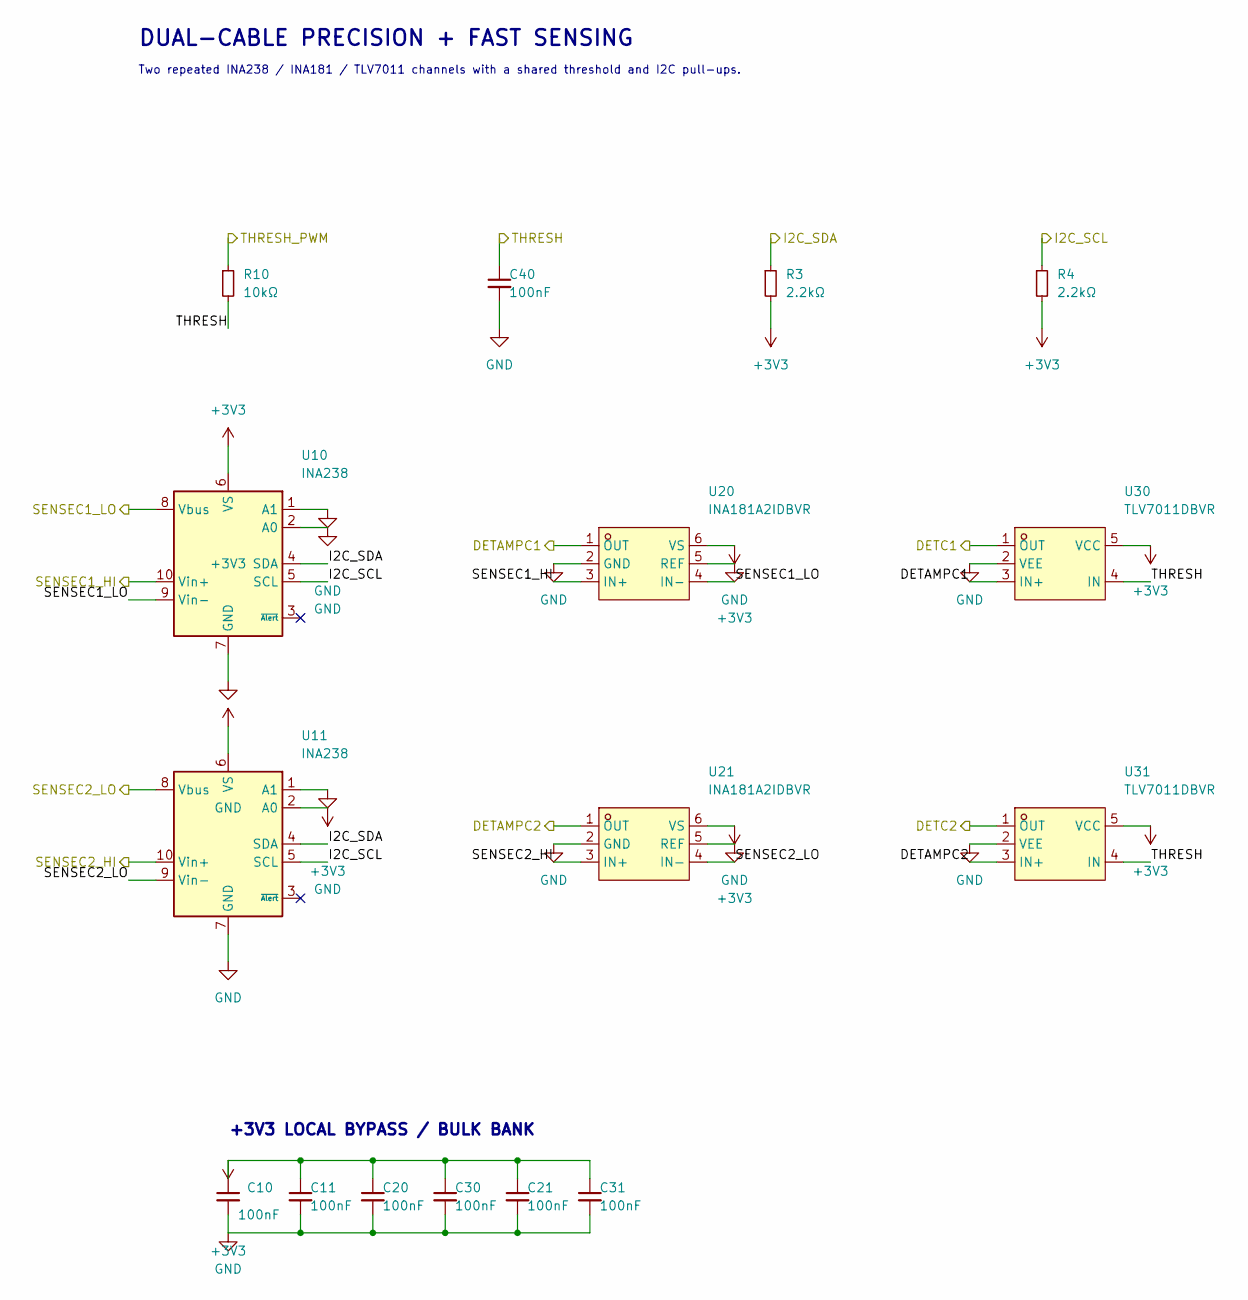
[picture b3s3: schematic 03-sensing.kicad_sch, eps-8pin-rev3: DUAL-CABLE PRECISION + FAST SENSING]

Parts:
C10, C11, C20, C21, C30, C31, C40: 100nF; C_0402_1005Metric; MPN CL05B104KO5NNNC; LCSC C1525
R3, R4: 2.2kΩ; R_0402_1005Metric; MPN 0402WGF2201TCE; LCSC C25879
R10: 10kΩ; R_0402_1005Metric; MPN 0402WGF1002TCE; LCSC C25744
U10, U11: INA238; VSSOP-10_3x3mm_P0.5mm; MPN INA238AIDGSR; LCSC C2868250
U20, U21: INA181A2IDBVR; SOT-23-6; MPN INA181A2IDBVR; LCSC C2058784
U30, U31: TLV7011DBVR; SOT-23-5; MPN TLV7011DBVR; LCSC C702117

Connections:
+3V3: C10.1, C11.1, C20.1, C21.1, C30.1, C31.1, R3.2, R4.2, U10.6 (VS), U11.2 (A0), U11.6 (VS), U20.6 (VS), U21.6 (VS), U30.5 (VCC), U31.5 (VCC); also elsewhere on the board
/DETAMPC1: U20.1 (OUT), U30.3 (IN+)
/DETAMPC2: U21.1 (OUT), U31.3 (IN+)
/DETC1: U30.1 (OUT); also elsewhere on the board
/DETC2: U31.1 (OUT); also elsewhere on the board
/I2C_SCL: R4.1, U10.5 (SCL), U11.5 (SCL); also elsewhere on the board
/I2C_SDA: R3.1, U10.4 (SDA), U11.4 (SDA); also elsewhere on the board
/SENSEC1_HI: U10.10 (Vin+), U20.3 (IN+); also elsewhere on the board
/SENSEC1_LO: U10.8 (Vbus), U10.9 (Vin-), U20.4 (IN-); also elsewhere on the board
/SENSEC2_HI: U11.10 (Vin+), U21.3 (IN+); also elsewhere on the board
/SENSEC2_LO: U11.8 (Vbus), U11.9 (Vin-), U21.4 (IN-); also elsewhere on the board
/THRESH: C40.1, R10.2, U30.4 (IN), U31.4 (IN)
/THRESH_PWM: R10.1; also elsewhere on the board

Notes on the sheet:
DUAL-CABLE PRECISION + FAST SENSING
Two repeated INA238 / INA181 / TLV7011 channels with a shared threshold and I2C pull-ups.
+3V3 LOCAL BYPASS / BULK BANK
